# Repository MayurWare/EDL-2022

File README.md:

# Electronic Design Lab (EDL)
## Department of Electrical Engineering, IIT Bombay
### Autumn 2021

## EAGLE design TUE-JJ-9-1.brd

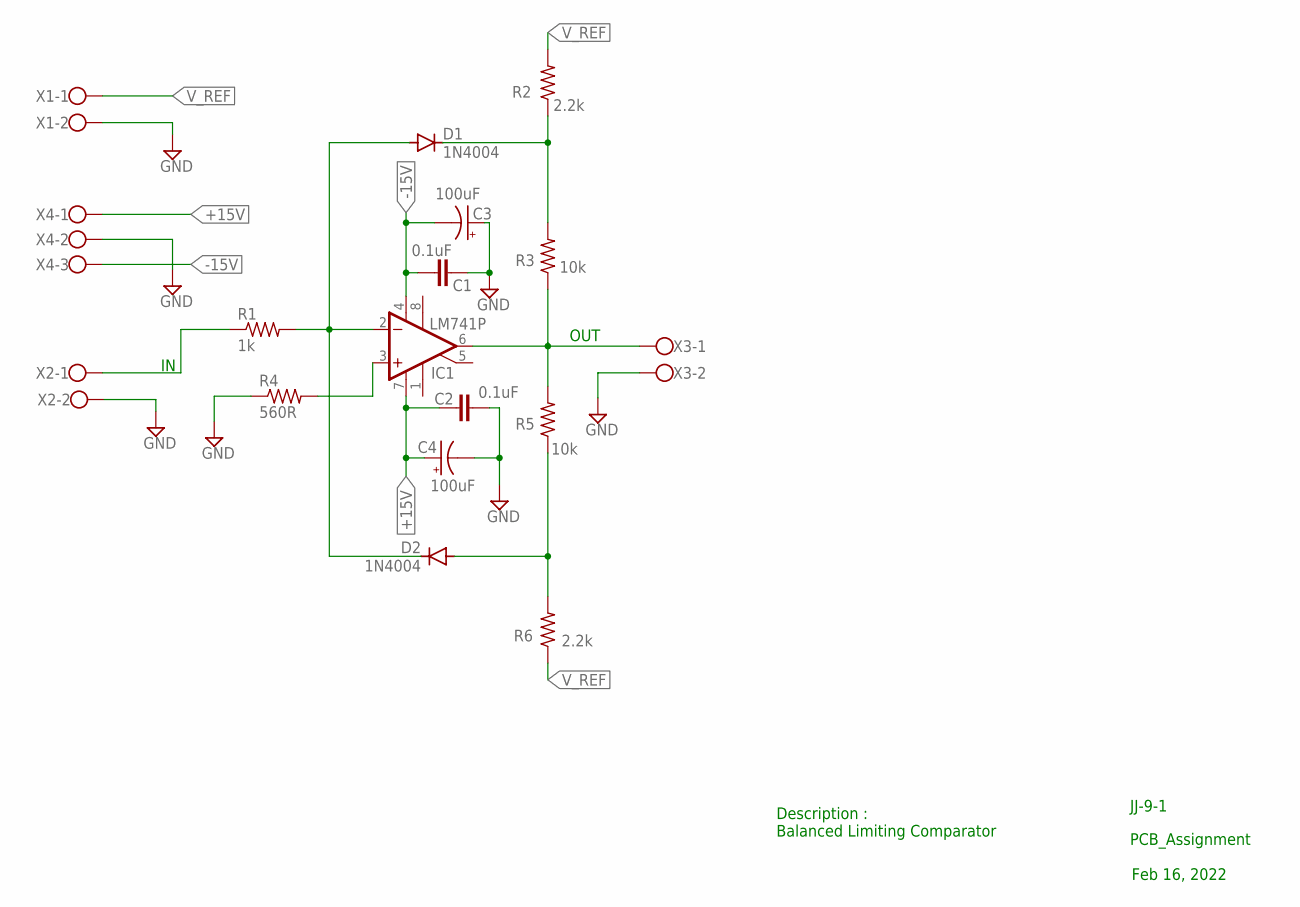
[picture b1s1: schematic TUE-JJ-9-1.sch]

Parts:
C1, C2: 0.1uF; C050-025X075
C3, C4: 100uF; E2,5-7
D1, D2: 1N4004; DO41-10
IC1: LM741P; DIL08
R1: 1k; 0207/10
R2, R6: 2.2k; 0207/10
R3, R5: 10k; 0207/10
R4: 560R; 0207/10
X1, X2, X3: W237-102
X4: W237-103

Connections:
+15V: C2.1, C4.+, IC1.7 (V+), X4.1
-15V: C1.1, C3.-, IC1.4 (V-), X4.3
GND: C1.2, C2.2, C3.+, C4.-, R4.1, X1.2, X2.2, X3.2, X4.2
unnamed: IC1.3 (+IN), R4.2
unnamed: D1.A, D2.C, IC1.2 (-IN), R1.2
unnamed: D1.C, R2.1, R3.2
unnamed: IC1.6 (OUT), R3.1, R5.2, X3.1
unnamed: D2.A, R5.1, R6.2
unnamed: R1.1, X2.1
V_REF: R2.2, R6.1, X1.1

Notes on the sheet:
OUT
JJ-9-1
PCB_Assignment
Feb 16, 2022
Description : Balanced Limiting Comparator

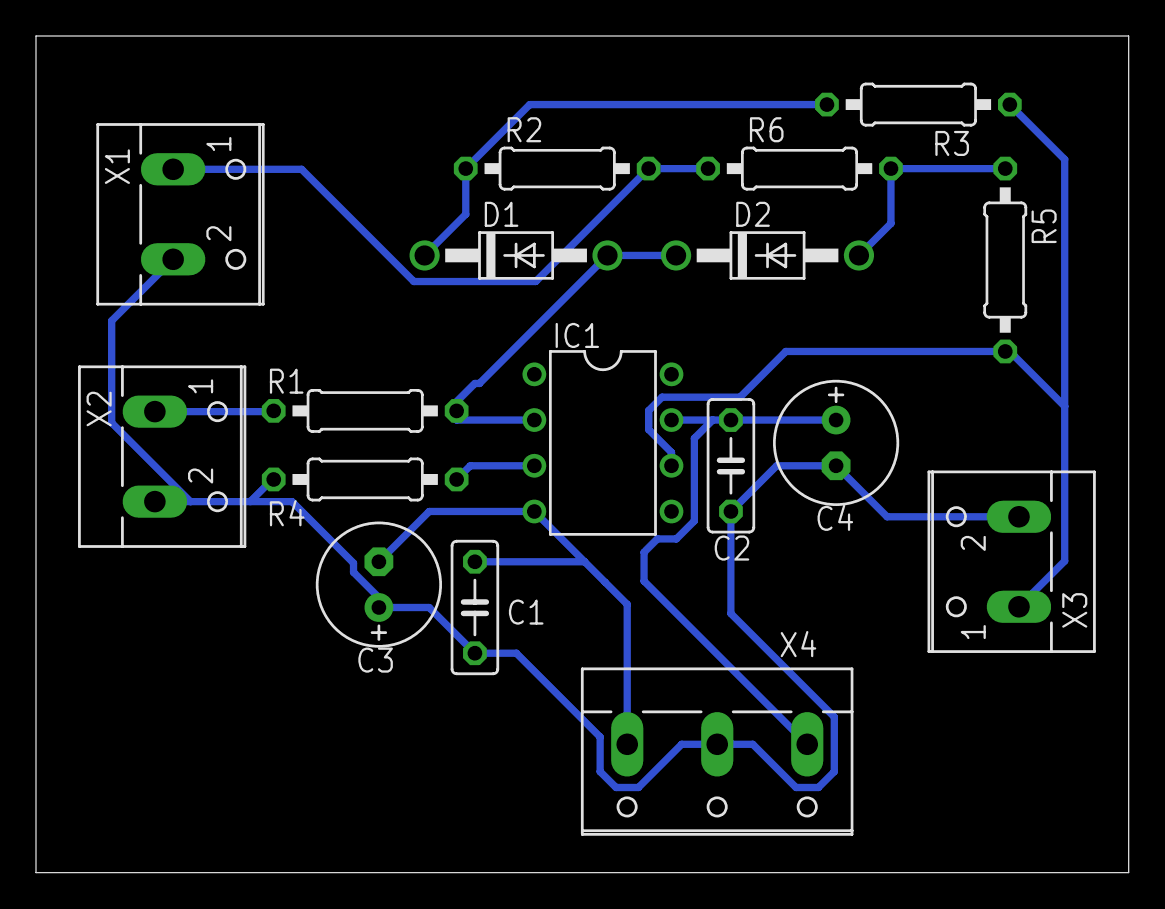
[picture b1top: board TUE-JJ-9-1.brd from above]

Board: 2 copper layers, 60.7 x 46.5 mm, 17 parts (0 on the bottom side), 10 nets.
